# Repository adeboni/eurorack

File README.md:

This repository stores various eurorack module designs I've made.

* BT Module: Allows you to pair your phone or computer and outputs stereo audio
* Dodecamodulator: 12 individually configurable LFOs through an onboard UI or through Bluetooth
* Geiger Clock Module: Uses a Geiger–Müller tube to generate pulses
* Google Assistant Module: A Google Home Mini in a eurorack form-factor
* Neopixel Controller Module: Can control neopixel rainbow cycle speed, brightness, and VU-meter-style amplitude with CV
* CS:GO Game State Integration Server: Receives events from CS:GO and enables gate outputs based on game states
* Safety Valve: Update of the GSMN Safety Safety Valve module with a trimmer to remove op-amp offset and added a socket for the tube
* ECG: Outputs a waveform from ECG electrodes plus a gate output with threshold adjustment

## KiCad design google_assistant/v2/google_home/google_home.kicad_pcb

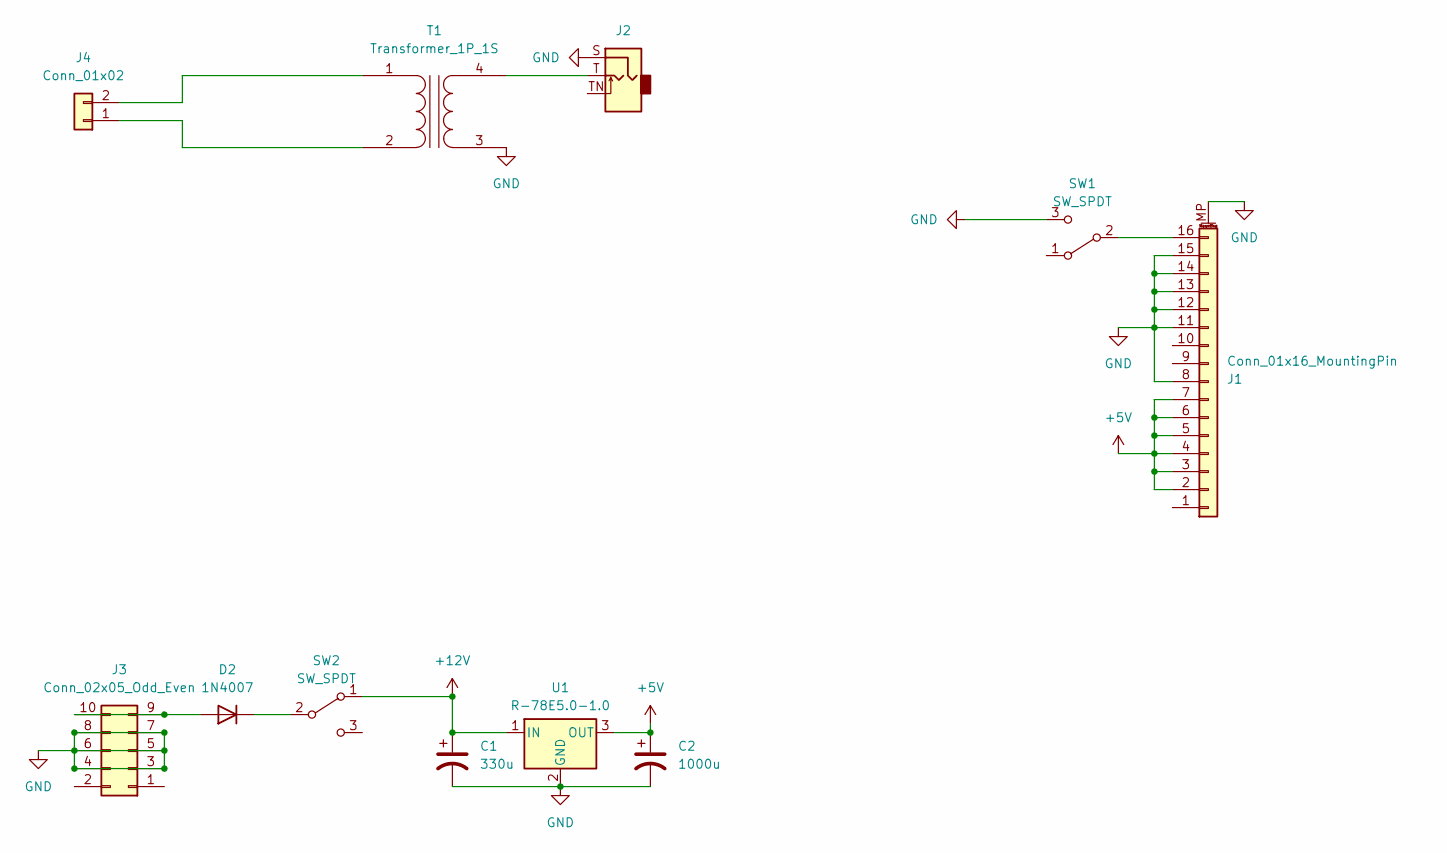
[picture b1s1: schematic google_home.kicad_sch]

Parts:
C1: 330u; CP_Radial_D8.0mm_P5.00mm
C2: 1000u; CP_Radial_D8.0mm_P5.00mm
D2: 1N4007; D_DO-41_SOD81_P10.16mm_Horizontal
J1: Conn_01x16_MountingPin; TE_1-1734839-6_1x16-1MP_P0.5mm_Horizontal
J2: AudioJack2_SwitchT; Jack_3.5mm_QingPu_WQP-PJ301M-12_Vertical
J3: Conn_02x05_Odd_Even; IDC-Header_2x05_P2.54mm_Vertical
J4: Conn_01x02; JST_XH_B2B-XH-A_1x02_P2.50mm_Vertical
SW1, SW2: SW_SPDT; Switch_Toggle_SPDT_Mini_SolderLug
T1: Transformer_1P_1S; EI14
U1: R-78E5.0-1.0; Converter_DCDC_RECOM_R-78E-0.5_THT

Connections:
+5V: C2.1, J1.2, J1.3, J1.4, J1.5, J1.6, J1.7, U1.3 (OUT)
+12V: C1.1, SW2.1 (A), U1.1 (IN)
GND: C1.2, C2.2, J1.8, J1.11, J1.12, J1.13, J1.14, J1.15, J1.MP (MountPin), J2.S, J3.3, J3.4, J3.5, J3.6, J3.7, J3.8, SW1.3 (C), T1.3 (SA), U1.2 (GND)
unnamed: D2.2 (A), J3.9, J3.10
unnamed: D2.1 (K), SW2.2 (B)
unnamed: J1.16, SW1.2 (B)
unnamed: J4.1, T1.2 (AB)
unnamed: J4.2, T1.1 (AA)
unnamed: J2.T, T1.4 (SB)

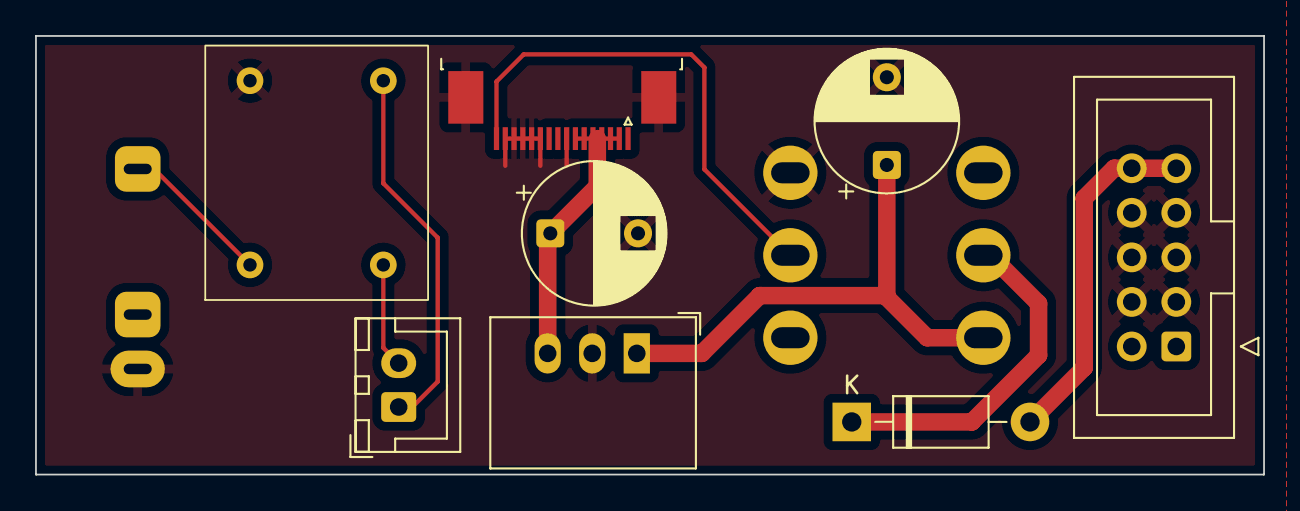
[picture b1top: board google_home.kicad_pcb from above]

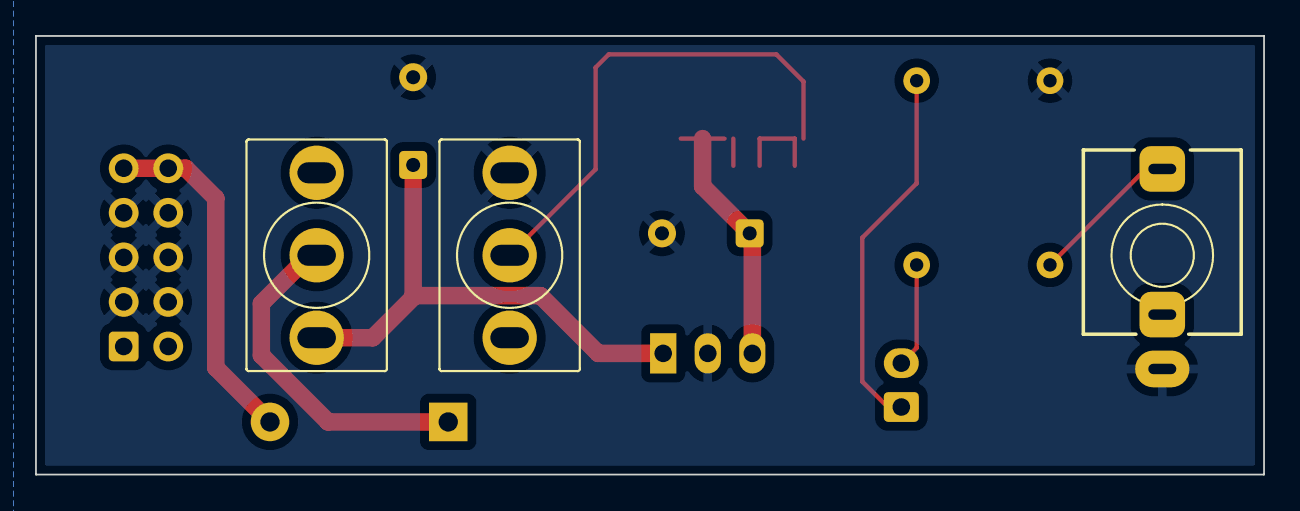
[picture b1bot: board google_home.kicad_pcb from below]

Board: 2 copper layers, 70.0 x 25.0 mm, 11 parts (3 on the bottom side), 9 nets.

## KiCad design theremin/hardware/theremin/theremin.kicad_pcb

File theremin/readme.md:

Based on https://github.com/GaudiLabs/OpenThereminV4, but combined the Eurorack functionality into the main board.
Note, the current PCB has the positions of the volume and pitch antenna connections reversed from the ideal positions.

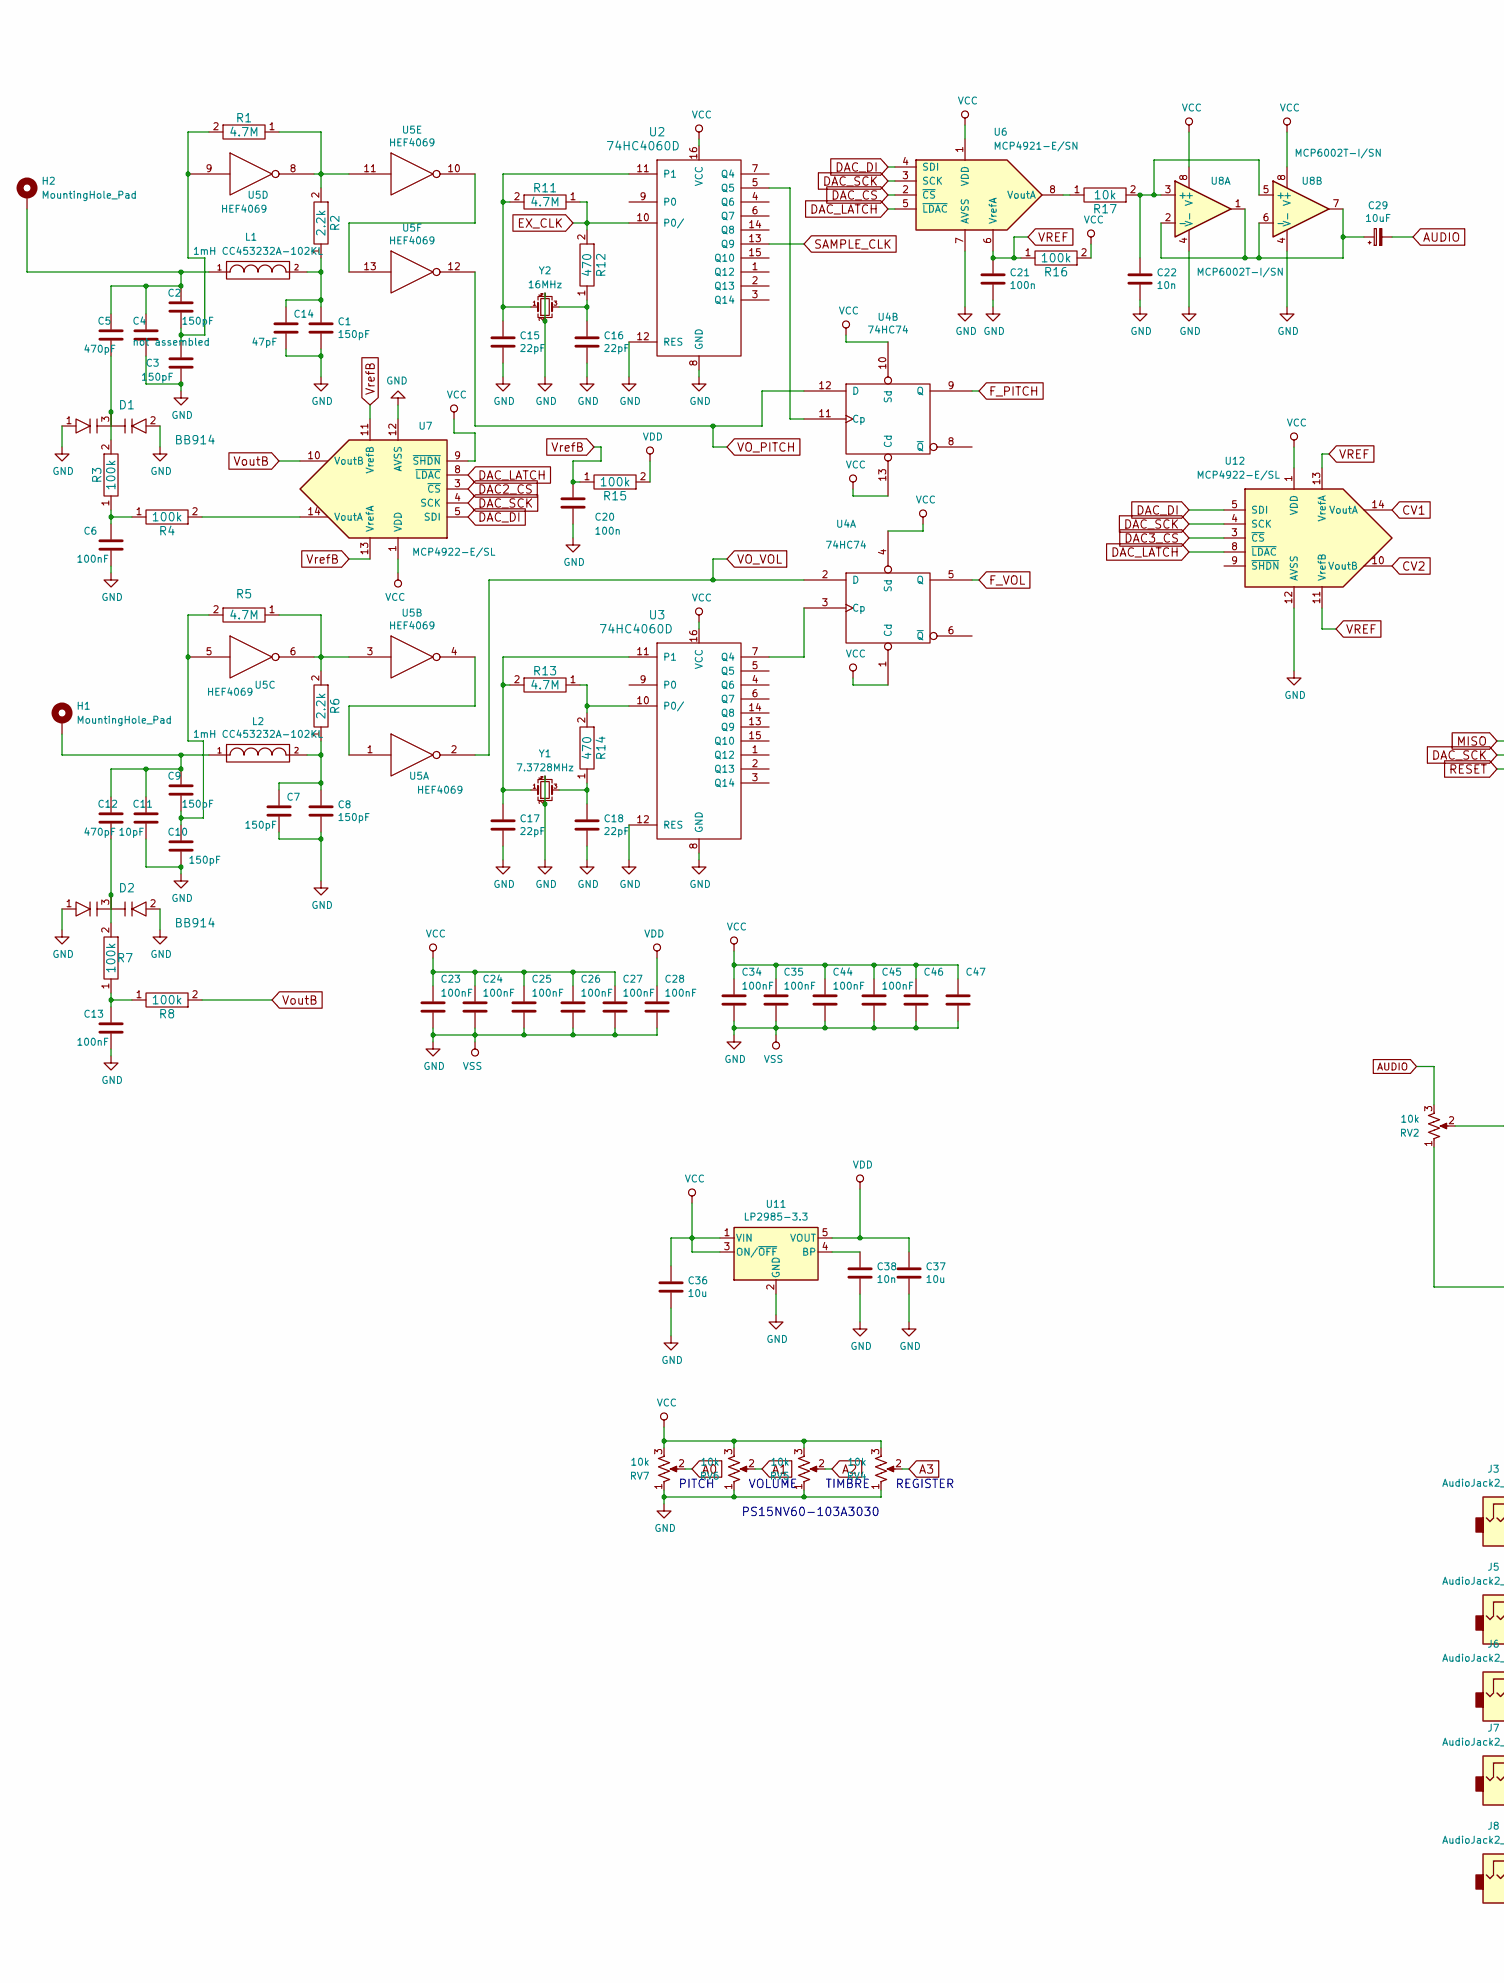
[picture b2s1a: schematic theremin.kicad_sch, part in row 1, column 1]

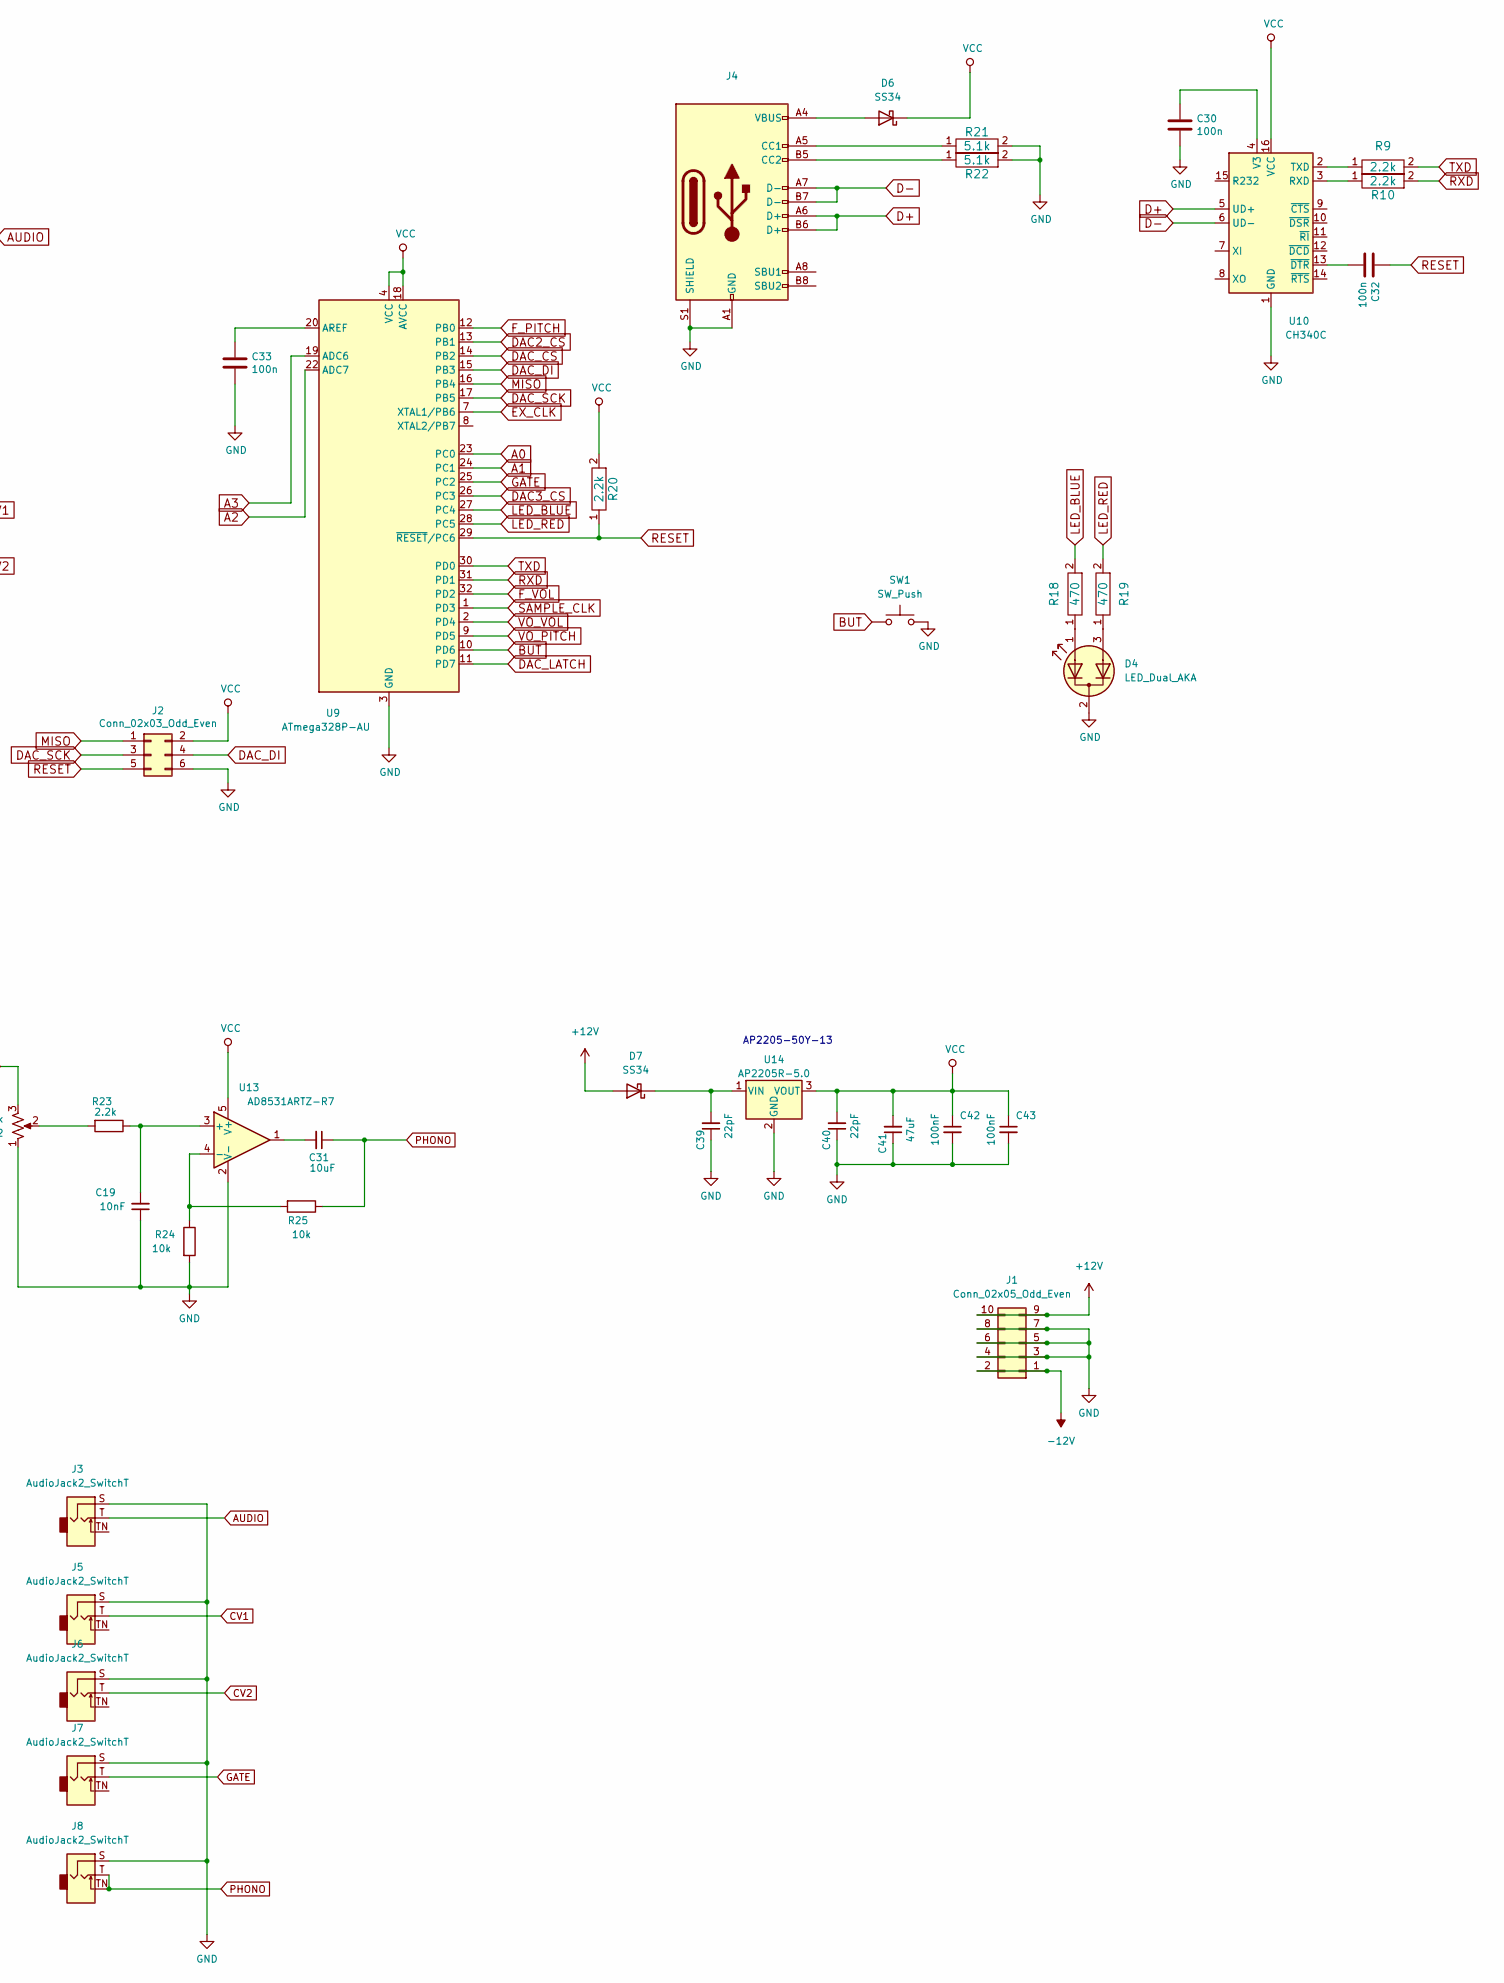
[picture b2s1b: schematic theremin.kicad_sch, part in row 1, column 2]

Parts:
C1, C2, C3, C7, C8, C9, C10: 150pF; C_0603_1608Metric
C4: not assembled; C_0603_1608Metric
C5, C12: 470pF; C_0603_1608Metric
C6, C13, C23, C24, C25, C26, C27, C28, C34, C35, C42, C43, C44, C45, C46, C47: 100nF; C_0603_1608Metric
C11: 10pF; C_0603_1608Metric
C14: 47pF; C_0603_1608Metric
C15, C16, C17, C18, C39, C40: 22pF; C_0603_1608Metric
C19: 10nF; C_0603_1608Metric
C20, C21, C30, C32, C33: 100n; C_0603_1608Metric
C22, C38: 10n; C_0603_1608Metric
C29, C31: 10uF; C_0603_1608Metric
C36, C37: 10u; C_0603_1608Metric
C41: 47uF; C_0805_2012Metric
D1, D2: BB914; SOT-23
D4: LED_Dual_AKA; LED_D5.0mm-3
D6, D7: SS34; D_SMA
H1, H2: MountingHole_Pad; MountingHole_3.2mm_M3_DIN965_Pad
J1: Conn_02x05_Odd_Even; IDC-Header_2x05_P2.54mm_Vertical
J2: Conn_02x03_Odd_Even; Tag-Connect_TC2030-IDC-NL_2x03_P1.27mm_Vertical
J3, J5, J6, J7, J8: AudioJack2_SwitchT; Jack_3.5mm_QingPu_WQP-PJ398SM_Vertical_CircularHoles
J4: USB_C_Receptacle_USB2.0_16P; USB_C_Receptacle_GCT_USB4105-xx-A_16P_TopMnt_Horizontal
L1, L2: 1mH CC453232A-102KL; C_1812_4532Metric
R1, R5, R11, R13: 4.7M; R_0603_1608Metric
R2, R6, R9, R10, R20, R23: 2.2k; R_0603_1608Metric
R3, R4, R7, R8, R15, R16: 100k; R_0603_1608Metric
R12, R14, R18, R19: 470; R_0603_1608Metric
R17, R24, R25: 10k; R_0603_1608Metric
R21, R22: 5.1k; R_0603_1608Metric
RV2, RV4, RV5, RV6, RV7: 10k; Potentiometer_Alpha_RD901F-40-00D_Single_Vertical
SW1: SW_Push; Push_E-Switch_KS01Q01
U2, U3: 74HC4060D; SOIC-16_3.9x9.9mm_P1.27mm
U4: 74HC74; SOIC-14_3.9x8.7mm_P1.27mm
U5: HEF4069; SOIC-14_3.9x8.7mm_P1.27mm
U6: MCP4921-E/SN; SOIC-8_3.9x4.9mm_P1.27mm
U7, U12: MCP4922-E/SL; SOIC-14_3.9x8.7mm_P1.27mm
U8: MCP6002T-I/SN; SOIC-8_3.9x4.9mm_P1.27mm
U9: ATmega328P-AU; TQFP-32_7x7mm_P0.8mm
U10: CH340C; SOIC-16_3.9x9.9mm_P1.27mm
U11: LP2985-3.3; SOT-23-5
U13: AD8531ARTZ-R7; SOT-23-5
U14: AP2205R-5.0; SOT-89-3
Y1: 7.3728MHz; Crystal_SMD_0603-4Pin_6.0x3.5mm
Y2: 16MHz; Crystal_SMD_0603-4Pin_6.0x3.5mm

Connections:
+12V: D7.2 (A), J1.9, J1.10
-12V: J1.1, J1.2
A0: RV7.2, U9.23 (PC0)
A1: RV6.2, U9.24 (PC1)
A2: RV5.2, U9.22 (ADC7)
A3: RV4.2, U9.19 (ADC6)
AUDIO: C29.2, J3.T, RV2.3
BUT: SW1.1, U9.10 (PD6)
CV1: J5.T, U12.14 (VoutA)
CV2: J6.T, U12.10 (VoutB)
D+: J4.A6 (D+), J4.B6 (D+), U10.5 (UD+)
D-: J4.A7 (D-), J4.B7 (D-), U10.6 (UD-)
DAC2_CS: U7.3 (~CS), U9.13 (PB1)
DAC3_CS: U9.26 (PC3), U12.3 (~CS)
DAC_CS: U6.2 (~CS), U9.14 (PB2)
DAC_DI: J2.4, U6.4 (SDI), U7.5 (SDI), U9.15 (PB3), U12.5 (SDI)
DAC_LATCH: U6.5 (~LDAC), U7.8 (~LDAC), U9.11 (PD7), U12.8 (~LDAC)
DAC_SCK: J2.3, U6.3 (SCK), U7.4 (SCK), U9.17 (PB5), U12.4 (SCK)
EX_CLK: R11.1, R12.2, U2.10 (P0/), U9.7 (XTAL1/PB6)
F_PITCH: U4.9 (Q), U9.12 (PB0)
F_VOL: U4.5 (Q), U9.32 (PD2)
GATE: J7.T, U9.25 (PC2)
GND: C1.2, C3.2, C4.2, C6.2, C7.2, C8.2, C10.2, C11.2, C13.2, C14.2, C15.2, C16.2, C17.2, C18.2, C19.1, C20.2, C21.2, C22.2, C23.2, C24.2, C25.2, C26.2, C27.2, C28.2, C30.2, C33.2, C34.2, C35.2, C36.2, C37.2, C38.2, C39.1, C40.1, C41.1, C42.2, C43.2, C44.2, C45.2, C46.2, C47.2, D1.1, D1.2, D2.1, D2.2, D4.2 (K), J1.3, J1.4, J1.5, J1.6, J1.7, J1.8, J2.6, J3.S, J4.A1 (GND), J4.A12 (GND), J4.B1 (GND), J4.B12 (GND), J4.S1 (SHIELD), J5.S, J6.S, J7.S, J8.S, R21.2, R22.2, R24.2, RV2.1, RV4.1, RV5.1, RV6.1, RV7.1, SW1.2, U2.8 (GND), U2.12 (RES), U3.8 (GND), U3.12 (RES), U4.7 (GND), U5.7 (VSS), U6.7 (AVSS), U7.12 (AVSS), U8.4 (V-), U9.3 (GND), U9.5 (GND), U9.21 (GND), U10.1 (GND), U11.2 (GND), U12.12 (AVSS), U13.2 (V-), U14.2 (GND), Y1.2, Y1.4, Y2.2, Y2.4
LED_BLUE: R18.2, U9.27 (PC4)
LED_RED: R19.2, U9.28 (PC5)
MISO: J2.1, U9.16 (PB4)
unnamed: C1.1, C14.1, L1.2, R2.1
unnamed: C2.1, C4.1, C5.1, H2.1, L1.1
unnamed: C2.2, C3.1, R1.2, U5.9
unnamed: C5.2, D1.3, R3.2
unnamed: C6.1, R3.1, R4.1
unnamed: C7.1, C8.1, L2.2, R6.1
unnamed: C9.2, C10.1, R5.2, U5.5
unnamed: C9.1, C11.1, C12.1, H1.1, L2.1
unnamed: C12.2, D2.3, R7.2
unnamed: C13.1, R7.1, R8.1
unnamed: C16.1, R12.1, Y2.3
unnamed: C18.1, R14.1, Y1.3
unnamed: C31.2, U13.1
unnamed: D4.1 (A1), R18.1
unnamed: D4.3 (A2), R19.1
unnamed: D6.2 (A), J4.A4 (VBUS), J4.A9 (VBUS), J4.B4 (VBUS), J4.B9 (VBUS)
unnamed: C39.2, D7.1 (K), U14.1 (VIN)
unnamed: J4.A5 (CC1), R21.1
unnamed: J4.B5 (CC2), R22.1
unnamed: R1.1, R2.2, U5.8, U5.11
unnamed: R5.1, R6.2, U5.3, U5.6
unnamed: R23.2, RV2.2
unnamed: C15.1, R11.2, U2.11 (P1), Y2.1
unnamed: U2.5 (Q5), U4.11 (Cp)
unnamed: R13.1, R14.2, U3.10 (P0/)
unnamed: C17.1, R13.2, U3.11 (P1), Y1.1
unnamed: U3.7 (Q4), U4.3 (Cp)
unnamed: U5.1, U5.4
unnamed: U5.10, U5.13
unnamed: R17.1, U6.8 (VoutA)
unnamed: R4.2, U7.14 (VoutA)
unnamed: C22.1, R17.2, U8.3 (+), U8.5 (+)
unnamed: C29.1, U8.1, U8.2 (-), U8.6 (-), U8.7
unnamed: C33.1, U9.20 (AREF)
unnamed: R10.1, U10.3 (RXD)
unnamed: R9.1, U10.2 (TXD)
unnamed: C30.1, U10.4 (V3)
unnamed: C32.2, U10.13 (~DTR)
unnamed: C38.1, U11.4 (BP)
unnamed: C19.2, R23.1, U13.3 (+)
unnamed: R24.1, R25.2, U13.4 (-)
PHONO: C31.1, J8.T, J8.TN, R25.1
RESET: C32.1, J2.5, R20.1, U9.29 (~RESET/PC6)
RXD: R10.2, U9.31 (PD1)
SAMPLE_CLK: U2.13 (Q9), U9.1 (PD3)
TXD: R9.2, U9.30 (PD0)
VCC: C23.1, C24.1, C25.1, C26.1, C27.1, C34.1, C35.1, C36.1, C40.2, C41.2, C42.1, C43.1, C44.1, C45.1, C46.1, C47.1, D6.1 (K), J2.2, R16.2, R20.2, RV4.3, RV5.3, RV6.3, RV7.3, U2.16 (VCC), U3.16 (VCC), U4.1 (Cd), U4.4 (Sd), U4.10 (Sd), U4.13 (Cd), U4.14 (VCC), U6.1 (VDD), U7.1 (VDD), U7.9 (~SHDN), U8.8 (V+), U9.4 (VCC), U9.6 (VCC), U9.18 (AVCC), U10.16 (VCC), U11.1 (VIN), U11.3 (ON/~OFF), U12.1 (VDD), U13.5 (V+), U14.3 (VOUT)
VDD: C28.1, C37.1, R15.2, U5.14 (VDD), U11.5 (VOUT)
VO_PITCH: U4.12 (D), U5.12, U9.9 (PD5)
VO_VOL: U4.2 (D), U5.2, U9.2 (PD4)
VREF: C21.1, R16.1, U6.6 (VrefA), U12.11 (VrefB), U12.13 (VrefA)
VoutB: R8.2, U7.10 (VoutB)
VrefB: C20.1, R15.1, U7.11 (VrefB), U7.13 (VrefA)

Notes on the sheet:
PITCH
AP2205-50Y-13
PS15NV60-103A3030
VOLUME
TIMBRE
REGISTER

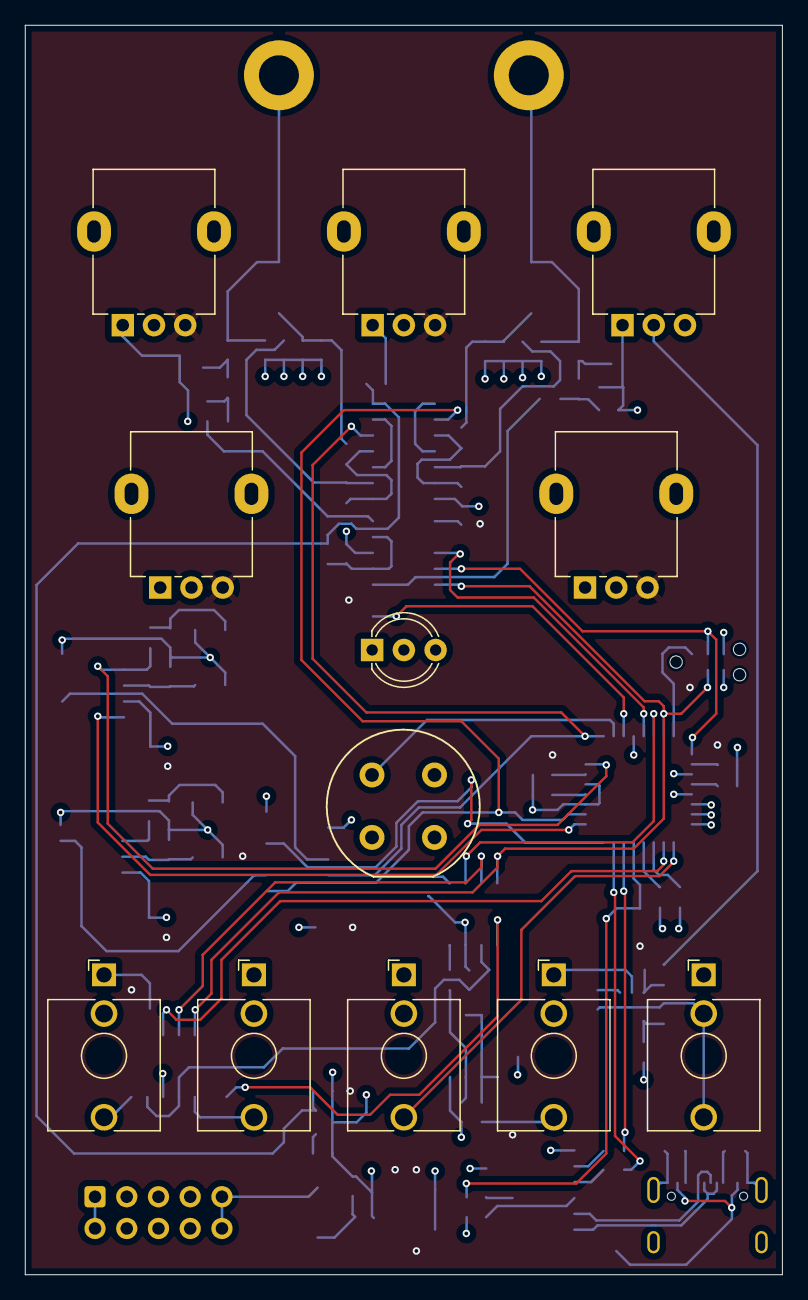
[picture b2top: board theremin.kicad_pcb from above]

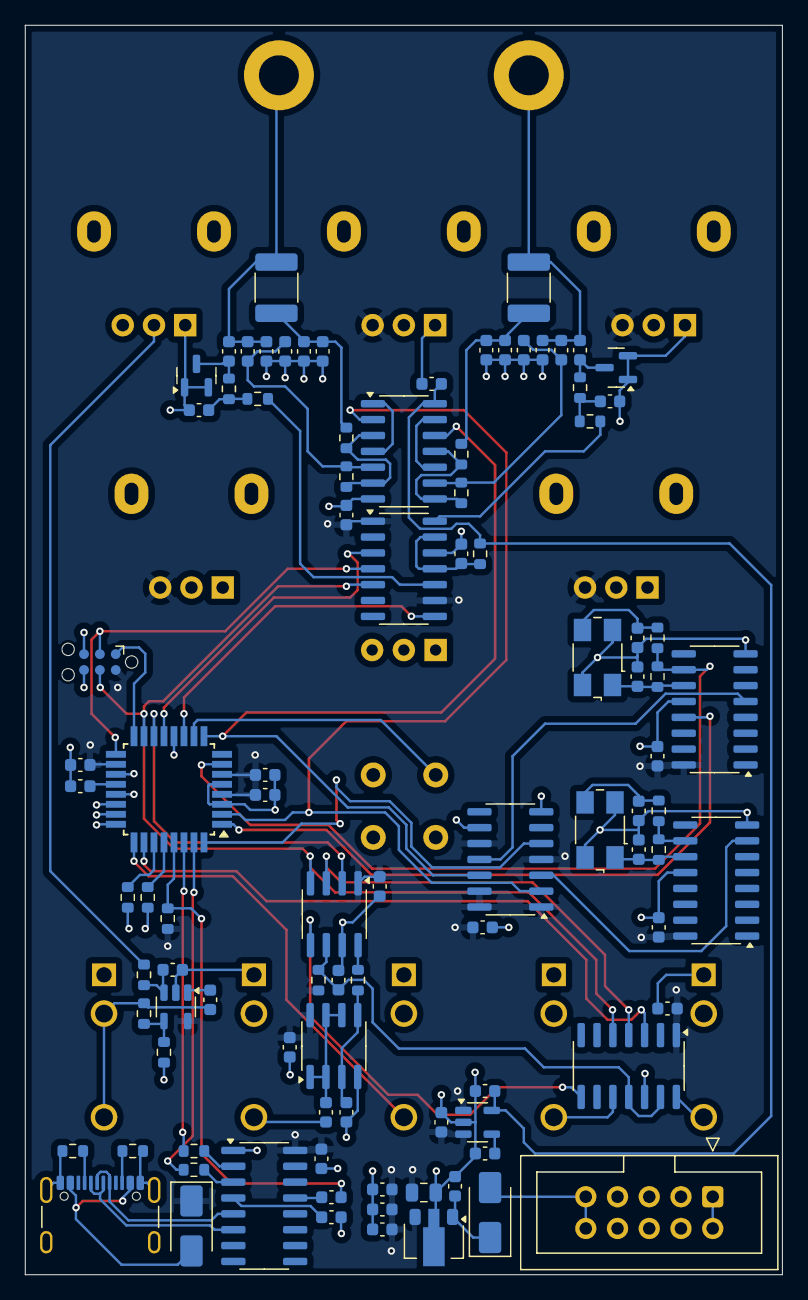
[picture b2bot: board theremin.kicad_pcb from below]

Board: 4 copper layers, 60.6 x 100.0 mm, 110 parts (98 on the bottom side), 79 nets.

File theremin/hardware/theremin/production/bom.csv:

Designator,Footprint,Quantity,Value,LCSC Part #
"C1, C10, C2, C3, C7, C8, C9",0603,7,150pF,
C11,0603,1,10pF,
"C12, C5",0603,2,470pF,
"C13, C23, C24, C25, C26, C27, C28, C34, C35, C42, C43, C44, C45, C46, C47, C6",0603,16,100nF,
C14,0603,1,47pF,
"C15, C16, C17, C18, C39, C40",0603,6,22pF,
C19,0603,1,10nF,
"C20, C21, C30, C32, C33",0603,5,100n,
"C22, C38",0603,2,10n,
"C29, C31",0603,2,10uF,
"C36, C37",0603,2,10u,
C4,0603,1,not assembled,
C41,0805,1,47uF,
"D1, D2",SOT-23,2,BB914,
D4,LED_D5.0mm-3,1,LED_Dual_AKA,
"D6, D7",D_SMA,2,SS34,
J1,IDC-Header_2x05_P2.54mm_Vertical,1,Conn_02x05_Odd_Even,
J2,Tag-Connect_TC2030-IDC-NL_2x03_P1.27mm_Vertical,1,Conn_02x03_Odd_Even,
"J3, J5, J6, J7, J8",Jack_3.5mm_QingPu_WQP-PJ398SM_Vertical_CircularHoles,5,AudioJack2_SwitchT,
J4,USB_C_Receptacle_GCT_USB4105-xx-A_16P_TopMnt_Horizontal,1,USB_C_Receptacle_USB2.0_16P,
"L1, L2",1812,2,1mH CC453232A-102KL,
"R1, R11, R13, R5",0603,4,4.7M,
"R10, R2, R20, R23, R6, R9",0603,6,2.2k,
"R12, R14, R18, R19",0603,4,470,
"R15, R16, R3, R4, R7, R8",0603,6,100k,
"R17, R24, R25",0603,3,10k,
"R21, R22",0603,2,5.1k,
"RV2, RV4, RV5, RV6, RV7",Potentiometer_Alpha_RD901F-40-00D_Single_Vertical,5,10k,
SW1,Push_E-Switch_KS01Q01,1,SW_Push,
U10,SOIC-16_3.9x9.9mm_P1.27mm,1,CH340C,
U11,SOT-23-5,1,LP2985-3.3,
"U12, U7",SOIC-14_3.9x8.7mm_P1.27mm,2,MCP4922-E/SL,
U13,SOT-23-5,1,AD8531ARTZ-R7,
U14,SOT-89-3,1,AP2205R-5.0,
"U2, U3",SOIC-16_3.9x9.9mm_P1.27mm,2,74HC4060D,
U4,SOIC-14_3.9x8.7mm_P1.27mm,1,74HC74,
U5,SOIC-14_3.9x8.7mm_P1.27mm,1,HEF4069,
U6,SOIC-8_3.9x4.9mm_P1.27mm,1,MCP4921-E/SN,
U8,SOIC-8_3.9x4.9mm_P1.27mm,1,MCP6002T-I/SN,
U9,TQFP-32_7x7mm_P0.8mm,1,ATmega328P-AU,
Y1,Crystal_SMD_0603-4Pin_6.0x3.5mm,1,7.3728MHz,
Y2,Crystal_SMD_0603-4Pin_6.0x3.5mm,1,16MHz,

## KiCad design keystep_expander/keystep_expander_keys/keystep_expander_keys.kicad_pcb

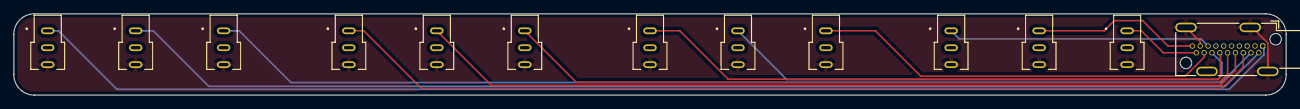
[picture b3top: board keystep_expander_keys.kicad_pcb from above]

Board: 2 copper layers, 188.0 x 12.0 mm, 13 parts (0 on the bottom side), 13 nets.

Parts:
J1, J2, J3, J4, J5, J6, J7, J8, J10, J11, J12, J13: AudioPlug3; CUI_SP-3533-02
J9: HDMI_A; HDMI_A_Kycon_KDMIX-SL1-NS-WS-B15_VerticalRightAngle

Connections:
G1: J1.T, J9.15 (SCL)
G2: J3.T, J9.12 (CK-)
G3: J5.T, J9.6 (D1-)
G4: J7.T, J9.1 (D2+)
GND: J1.S, J2.S, J3.S, J4.S, J5.S, J6.S, J7.S, J8.S, J9.17 (GND), J9.SH, J10.S, J11.S, J12.S, J13.S
M1: J2.T, J9.19 (HPD)
M2: J4.T, J9.14 (UTILITY)
M3: J6.T, J9.8 (D0S)
M4: J8.T, J9.2 (D2S)
P1: J9.18 (+5V), J10.T
P2: J9.16 (SDA), J11.T
P3: J9.10 (CK+), J12.T
P4: J9.4 (D1+), J13.T

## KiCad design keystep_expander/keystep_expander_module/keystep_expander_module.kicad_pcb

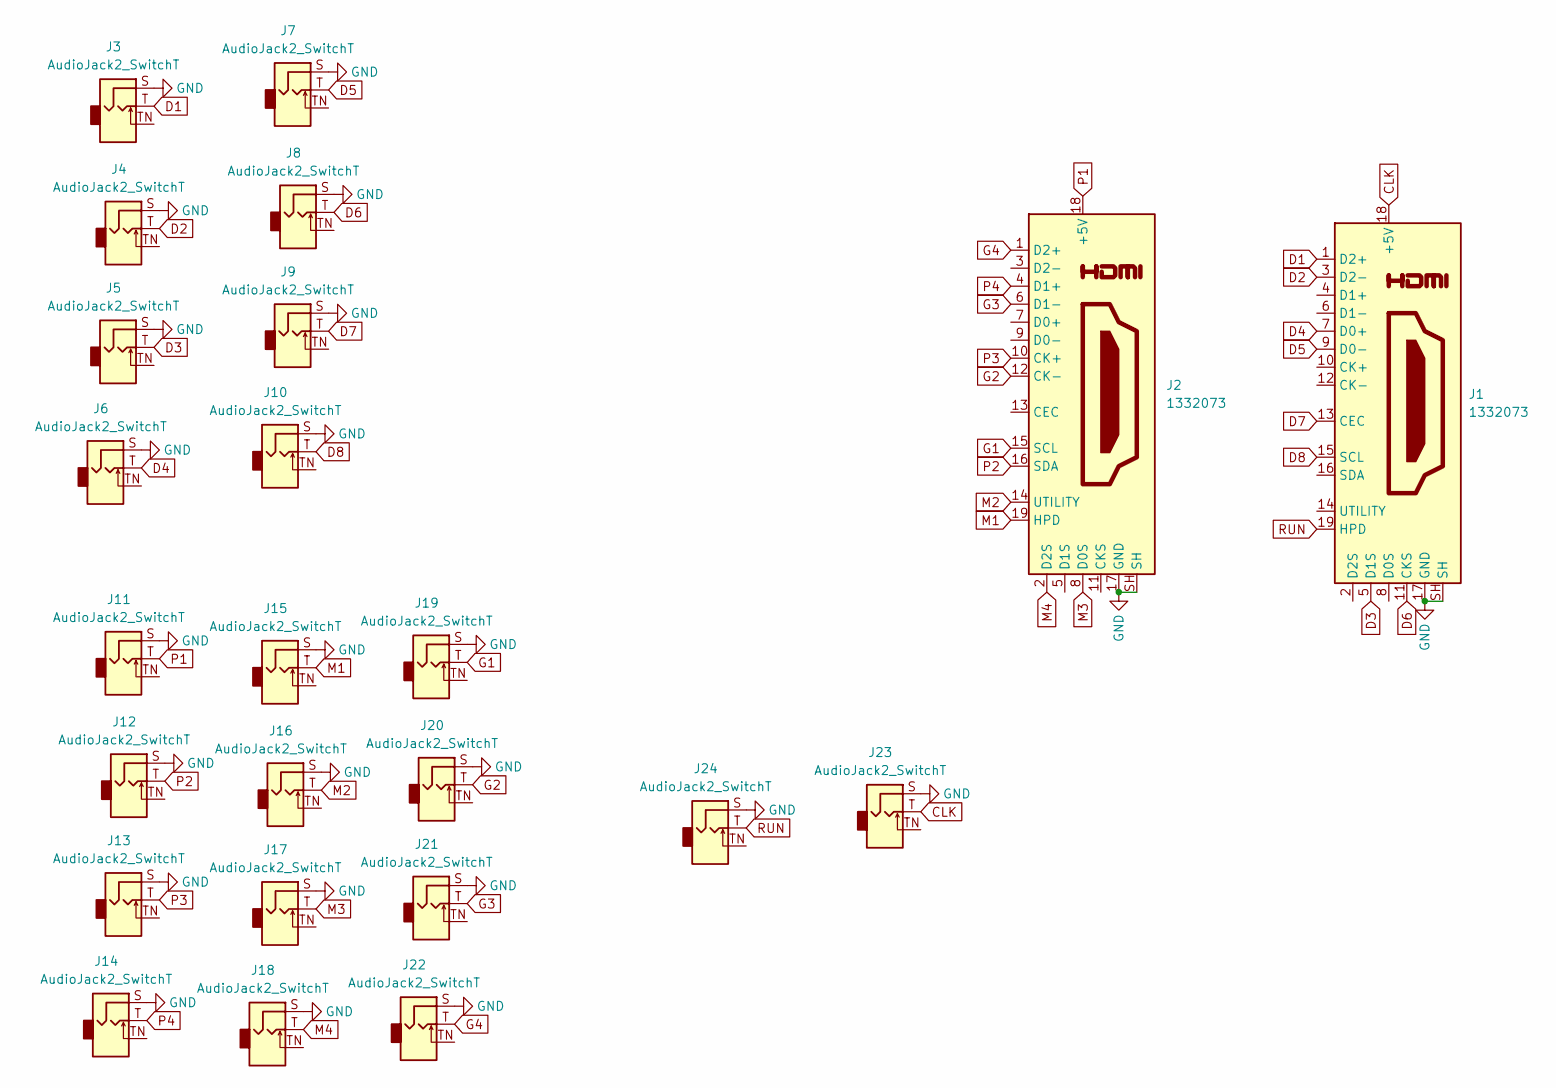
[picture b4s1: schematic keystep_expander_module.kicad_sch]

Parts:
J1, J2: 1332073; PHOENIX_1332073
J3, J4, J5, J6, J7, J8, J9, J10, J11, J12, J13, J14, J15, J16, J17, J18, J19, J20, J21, J22, J23, J24: AudioJack2_SwitchT; Jack_3.5mm_QingPu_WQP-PJ398SM_Vertical_CircularHoles

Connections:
CLK: J1.18 (+5V), J23.T
D1: J1.1 (D2+), J3.T
D2: J1.3 (D2-), J4.T
D3: J1.5 (D1S), J5.T
D4: J1.7 (D0+), J6.T
D5: J1.9 (D0-), J7.T
D6: J1.11 (CKS), J8.T
D7: J1.13 (CEC), J9.T
D8: J1.15 (SCL), J10.T
G1: J2.15 (SCL), J19.T
G2: J2.12 (CK-), J20.T
G3: J2.6 (D1-), J21.T
G4: J2.1 (D2+), J22.T
GND: J1.17 (GND), J1.SH, J2.17 (GND), J2.SH, J3.S, J4.S, J5.S, J6.S, J7.S, J8.S, J9.S, J10.S, J11.S, J12.S, J13.S, J14.S, J15.S, J16.S, J17.S, J18.S, J19.S, J20.S, J21.S, J22.S, J23.S, J24.S
M1: J2.19 (HPD), J15.T
M2: J2.14 (UTILITY), J16.T
M3: J2.8 (D0S), J17.T
M4: J2.2 (D2S), J18.T
P1: J2.18 (+5V), J11.T
P2: J2.16 (SDA), J12.T
P3: J2.10 (CK+), J13.T
P4: J2.4 (D1+), J14.T
RUN: J1.19 (HPD), J24.T

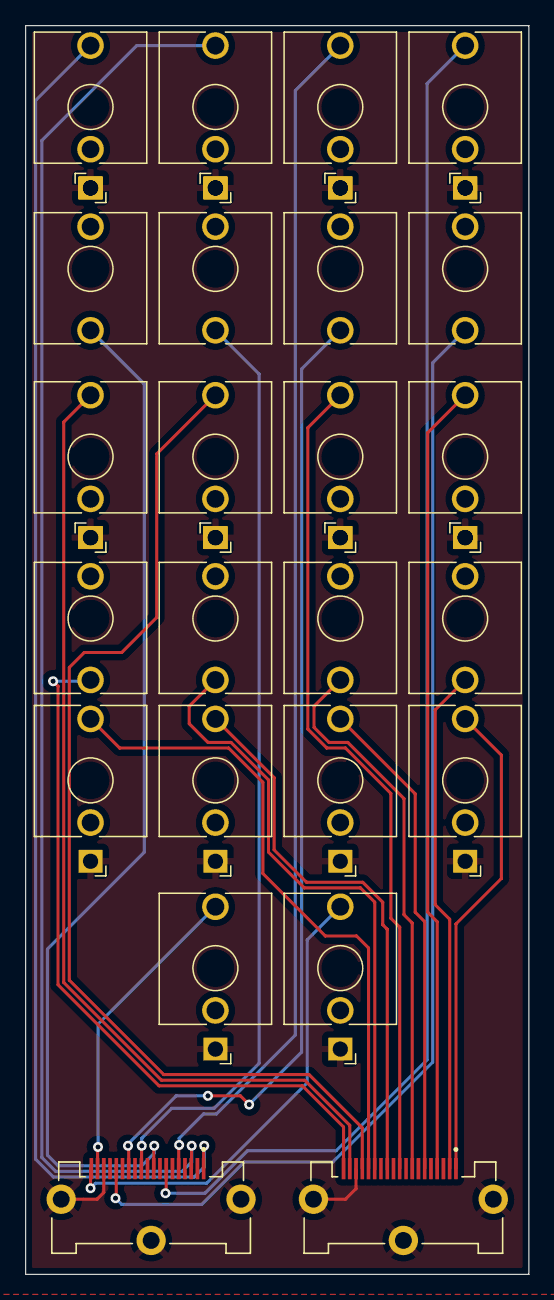
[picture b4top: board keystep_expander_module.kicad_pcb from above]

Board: 2 copper layers, 40.3 x 100.0 mm, 24 parts (0 on the bottom side), 23 nets.

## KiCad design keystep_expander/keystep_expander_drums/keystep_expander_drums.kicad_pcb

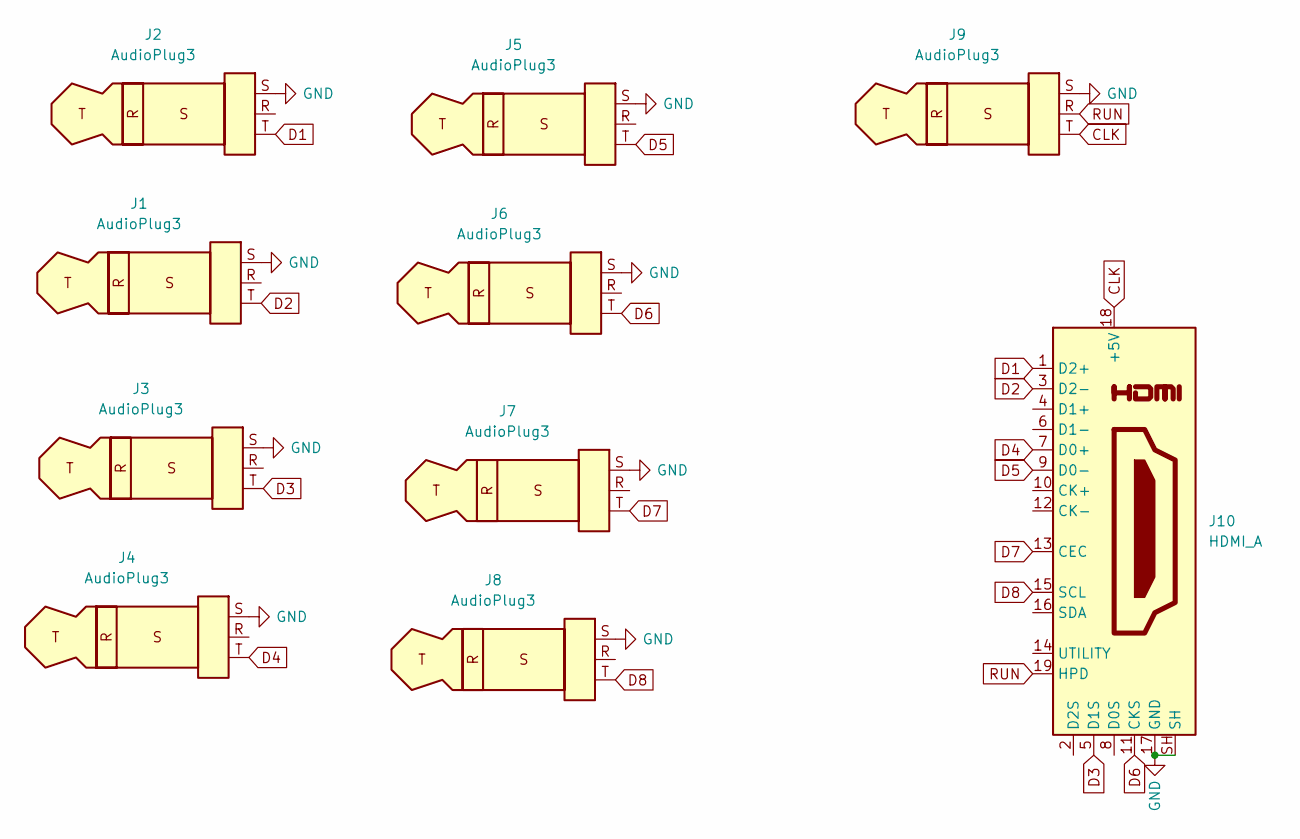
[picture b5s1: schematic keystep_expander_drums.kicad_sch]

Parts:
J1, J2, J3, J4, J5, J6, J7, J8, J9: AudioPlug3; CUI_SP-3533-02
J10: HDMI_A; HDMI_A_Kycon_KDMIX-SL1-NS-WS-B15_VerticalRightAngle

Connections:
CLK: J9.T, J10.18 (+5V)
D1: J2.T, J10.1 (D2+)
D2: J1.T, J10.3 (D2-)
D3: J3.T, J10.5 (D1S)
D4: J4.T, J10.7 (D0+)
D5: J5.T, J10.9 (D0-)
D6: J6.T, J10.11 (CKS)
D7: J7.T, J10.13 (CEC)
D8: J8.T, J10.15 (SCL)
GND: J1.S, J2.S, J3.S, J4.S, J5.S, J6.S, J7.S, J8.S, J9.S, J10.17 (GND), J10.SH
RUN: J9.R, J10.19 (HPD)

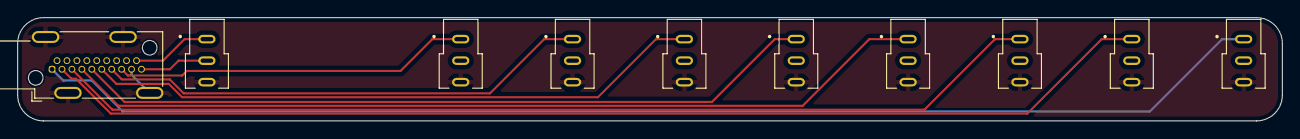
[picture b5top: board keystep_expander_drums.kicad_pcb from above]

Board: 2 copper layers, 147.0 x 12.0 mm, 10 parts (0 on the bottom side), 11 nets.

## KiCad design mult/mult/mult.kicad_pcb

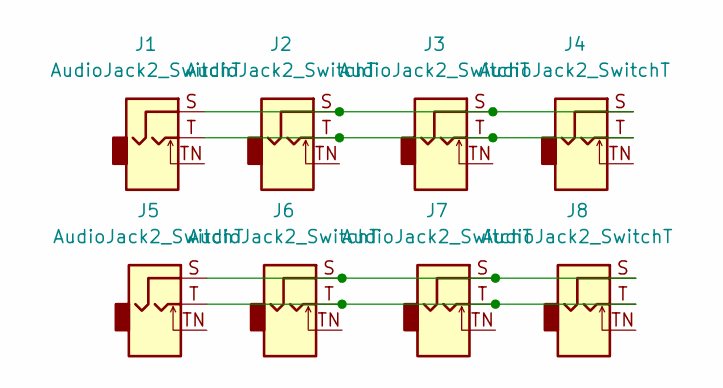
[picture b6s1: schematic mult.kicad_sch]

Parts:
J1, J2, J3, J4, J5, J6, J7, J8: AudioJack2_SwitchT; Jack_3.5mm_QingPu_WQP-PJ398SM_Vertical_CircularHoles

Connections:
unnamed: J1.S, J2.S, J3.S, J4.S
unnamed: J1.T, J2.T, J3.T, J4.T
unnamed: J5.S, J6.S, J7.S, J8.S
unnamed: J5.T, J6.T, J7.T, J8.T

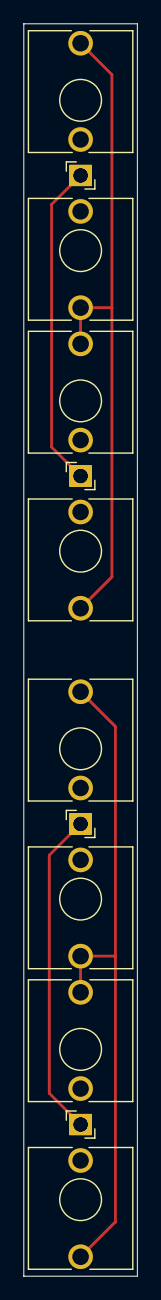
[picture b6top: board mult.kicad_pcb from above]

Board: 2 copper layers, 9.8 x 108.0 mm, 8 parts (0 on the bottom side), 4 nets.
